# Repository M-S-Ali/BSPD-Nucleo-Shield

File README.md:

# BSPD-Nucleo-Shield
Modern vehicles use an accelerator pedal to control the engine’s throttle, which regulates power output. Traditionally, this was achieved through complex mechanical linkages. However, relying solely on the accelerator pedal is not the most efficient way to determine engine power, as other factors like fuel injection and combustion also play a critical role. 

To address this, modern vehicles use **throttle-by-wire systems**, where the accelerator pedal sends electronic signals to a vehicle control unit (VCU). The VCU processes these signals along with other engine parameters to optimize power output. While this approach improves efficiency and performance, it introduces concerns such as potential wire disconnections or data transmission errors. 

In high-performance applications, like racing, safety mechanisms such as the **Brake System Plausibility Device (BSPD)** are used to mitigate risks by cutting off engine power if a fault is detected.

This project focuses on designing an **enhanced throttle-by-wire system** with integrated BSPD functionality. The system is implemented using an **STM32 Nucleo board**, programmed through **MATLAB Simulink**, and employs **fuzzy logic** for intelligent control. A custom-designed **PCB shield** ensures seamless integration with the hardware for practical implementation.

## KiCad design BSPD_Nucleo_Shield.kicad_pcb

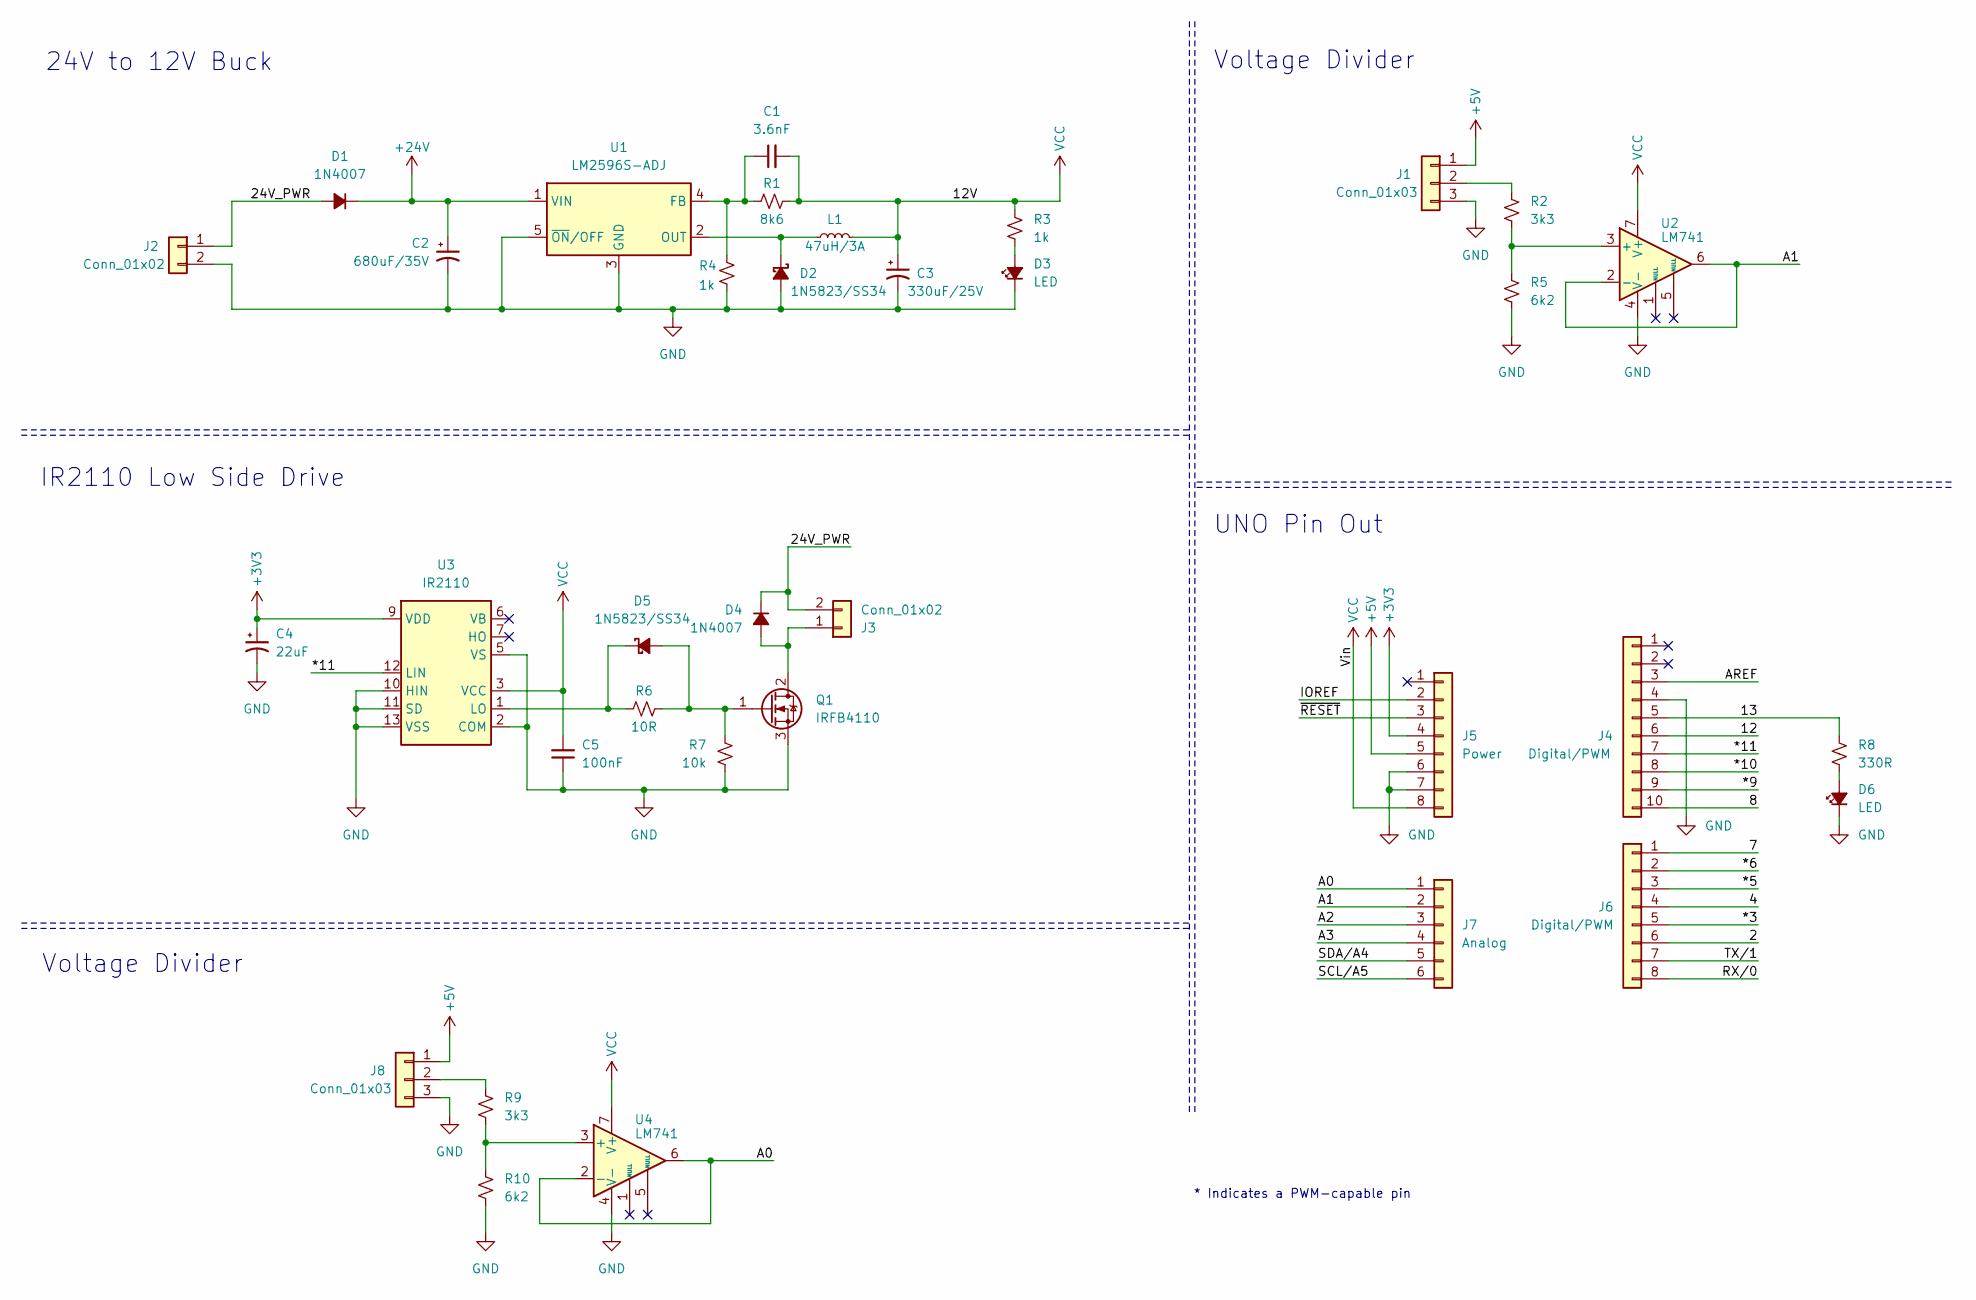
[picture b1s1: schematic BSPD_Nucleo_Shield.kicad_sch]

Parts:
C1: 3.6nF; C_Disc_D3.0mm_W2.0mm_P2.50mm
C2: 680uF/35V; CP_Radial_D10.0mm_P5.00mm
C3: 330uF/25V; CP_Radial_D8.0mm_P3.50mm
C4: 22uF; CP_Radial_D5.0mm_P2.00mm
C5: 100nF; C_Disc_D3.0mm_W2.0mm_P2.50mm
D1, D4: 1N4007; D_DO-41_SOD81_P10.16mm_Horizontal
D2, D5: 1N5823/SS34; D_SMA_Handsoldering
D3, D6: LED; LED_D3.0mm
J1, J8: Conn_01x03; TerminalBlock_bornier-3_P5.08mm
J2, J3: Conn_01x02; TerminalBlock_bornier-2_P5.08mm
J4: Digital/PWM; PinHeader_1x10_P2.54mm_Vertical
J5: Power; PinHeader_1x08_P2.54mm_Vertical
J6: Digital/PWM; PinHeader_1x08_P2.54mm_Vertical
J7: Analog; PinHeader_1x06_P2.54mm_Vertical
L1: 47uH/3A; L_12x12mm_H8mm
Q1: IRFB4110; TO-220-3_Vertical
R1: 8k6; R_Axial_DIN0207_L6.3mm_D2.5mm_P10.16mm_Horizontal
R2, R9: 3k3; R_Axial_DIN0207_L6.3mm_D2.5mm_P10.16mm_Horizontal
R3, R4: 1k; R_Axial_DIN0207_L6.3mm_D2.5mm_P10.16mm_Horizontal
R5, R10: 6k2; R_Axial_DIN0207_L6.3mm_D2.5mm_P10.16mm_Horizontal
R6: 10R; R_Axial_DIN0207_L6.3mm_D2.5mm_P10.16mm_Horizontal
R7: 10k; R_Axial_DIN0207_L6.3mm_D2.5mm_P10.16mm_Horizontal
R8: 330R; R_Axial_DIN0207_L6.3mm_D2.5mm_P10.16mm_Horizontal
U1: LM2596S-ADJ; TO-263-5_TabPin3
U2, U4: LM741; DIP-8_W7.62mm_LongPads
U3: IR2110; DIP-14_W7.62mm_LongPads

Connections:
+3V3: C4.1, J5.4, U3.9 (VDD)
+5V: J1.1, J5.5, J8.1
+24V: C2.1, D1.1 (K), U1.1 (VIN)
/2: J6.6
/4: J6.4
/7: J6.1
/8: J4.10
/12: J4.6
/13: J4.5, R8.1
/24V_PWR: D1.2 (A), D4.1 (K), J2.1, J3.2
/*3: J6.5
/*5: J6.3
/*6: J6.2
/*9: J4.9
/*10: J4.8
/*11: J4.7, U3.12 (LIN)
/A0: J7.1, U4.2 (-), U4.6
/A1: J7.2, U2.2 (-), U2.6
/A2: J7.3
/A3: J7.4
/AREF: J4.3
/IOREF: J5.2
/RX/0: J6.8
/SCL/A5: J7.6
/SDA/A4: J7.5
/TX/1: J6.7
/~RESET: J5.3
GND: C2.2, C3.2, C4.2, C5.1, D2.2 (A), D3.1 (K), D6.1 (K), J1.3, J2.2, J4.4, J5.6, J5.7, J8.3, Q1.3 (S), R4.2, R5.2, R7.2, R10.2, U1.3 (GND), U1.5 (~ON/OFF), U2.4 (V-), U3.2 (COM), U3.5 (VS), U3.10 (HIN), U3.11 (SD), U3.13 (VSS), U4.4 (V-)
unnamed: D2.1 (K), L1.1, U1.2 (OUT)
unnamed: D3.2 (A), R3.2
unnamed: D4.2 (A), J3.1, Q1.2 (D)
unnamed: D5.2 (A), Q1.1 (G), R6.2, R7.1
unnamed: D5.1 (K), R6.1, U3.1 (LO)
unnamed: D6.2 (A), R8.2
unnamed: J1.2, R2.1
unnamed: J8.2, R9.1
unnamed: C1.1, R1.1, R4.1, U1.4 (FB)
unnamed: R2.2, R5.1, U2.3 (+)
unnamed: R9.2, R10.1, U4.3 (+)
VCC: C1.2, C3.1, C5.2, J5.8, L1.2, R1.2, R3.1, U2.7 (V+), U3.3 (VCC), U4.7 (V+)

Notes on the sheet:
Voltage Divider
IR2110 Low Side Drive
* Indicates a PWM-capable pin
24V to 12V Buck
UNO Pin Out

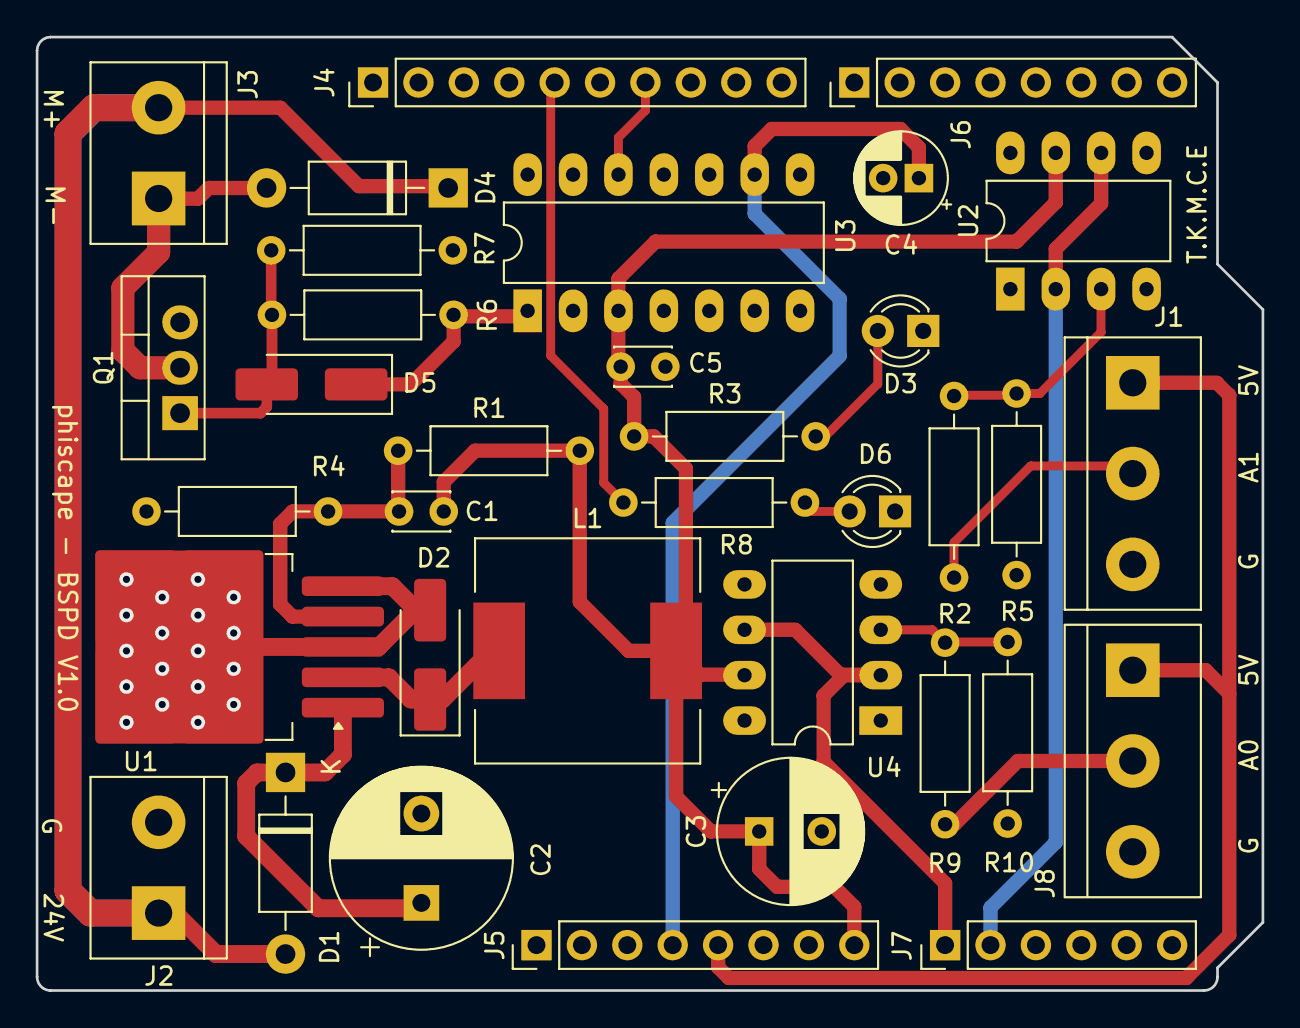
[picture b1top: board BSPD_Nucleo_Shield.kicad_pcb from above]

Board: 2 copper layers, 68.6 x 53.3 mm, 35 parts (0 on the bottom side), 21 nets.

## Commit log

2024-03-21 initial upload
2024-03-21 updated to kicad8.0.1
2024-03-22 v1.0 released
    placed order for 5 from lion circuits
2025-01-05 Included MATLAB Files
